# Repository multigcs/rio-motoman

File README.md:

# rio-octobot
6Axis LinuxCNC-RIO main-board - for the iceWerx iCE40-HX8K FPGA-Devboard - kicad project 
 
experimental - not tested yet

 https://youtube.com/shorts/BiJppd6_cA4

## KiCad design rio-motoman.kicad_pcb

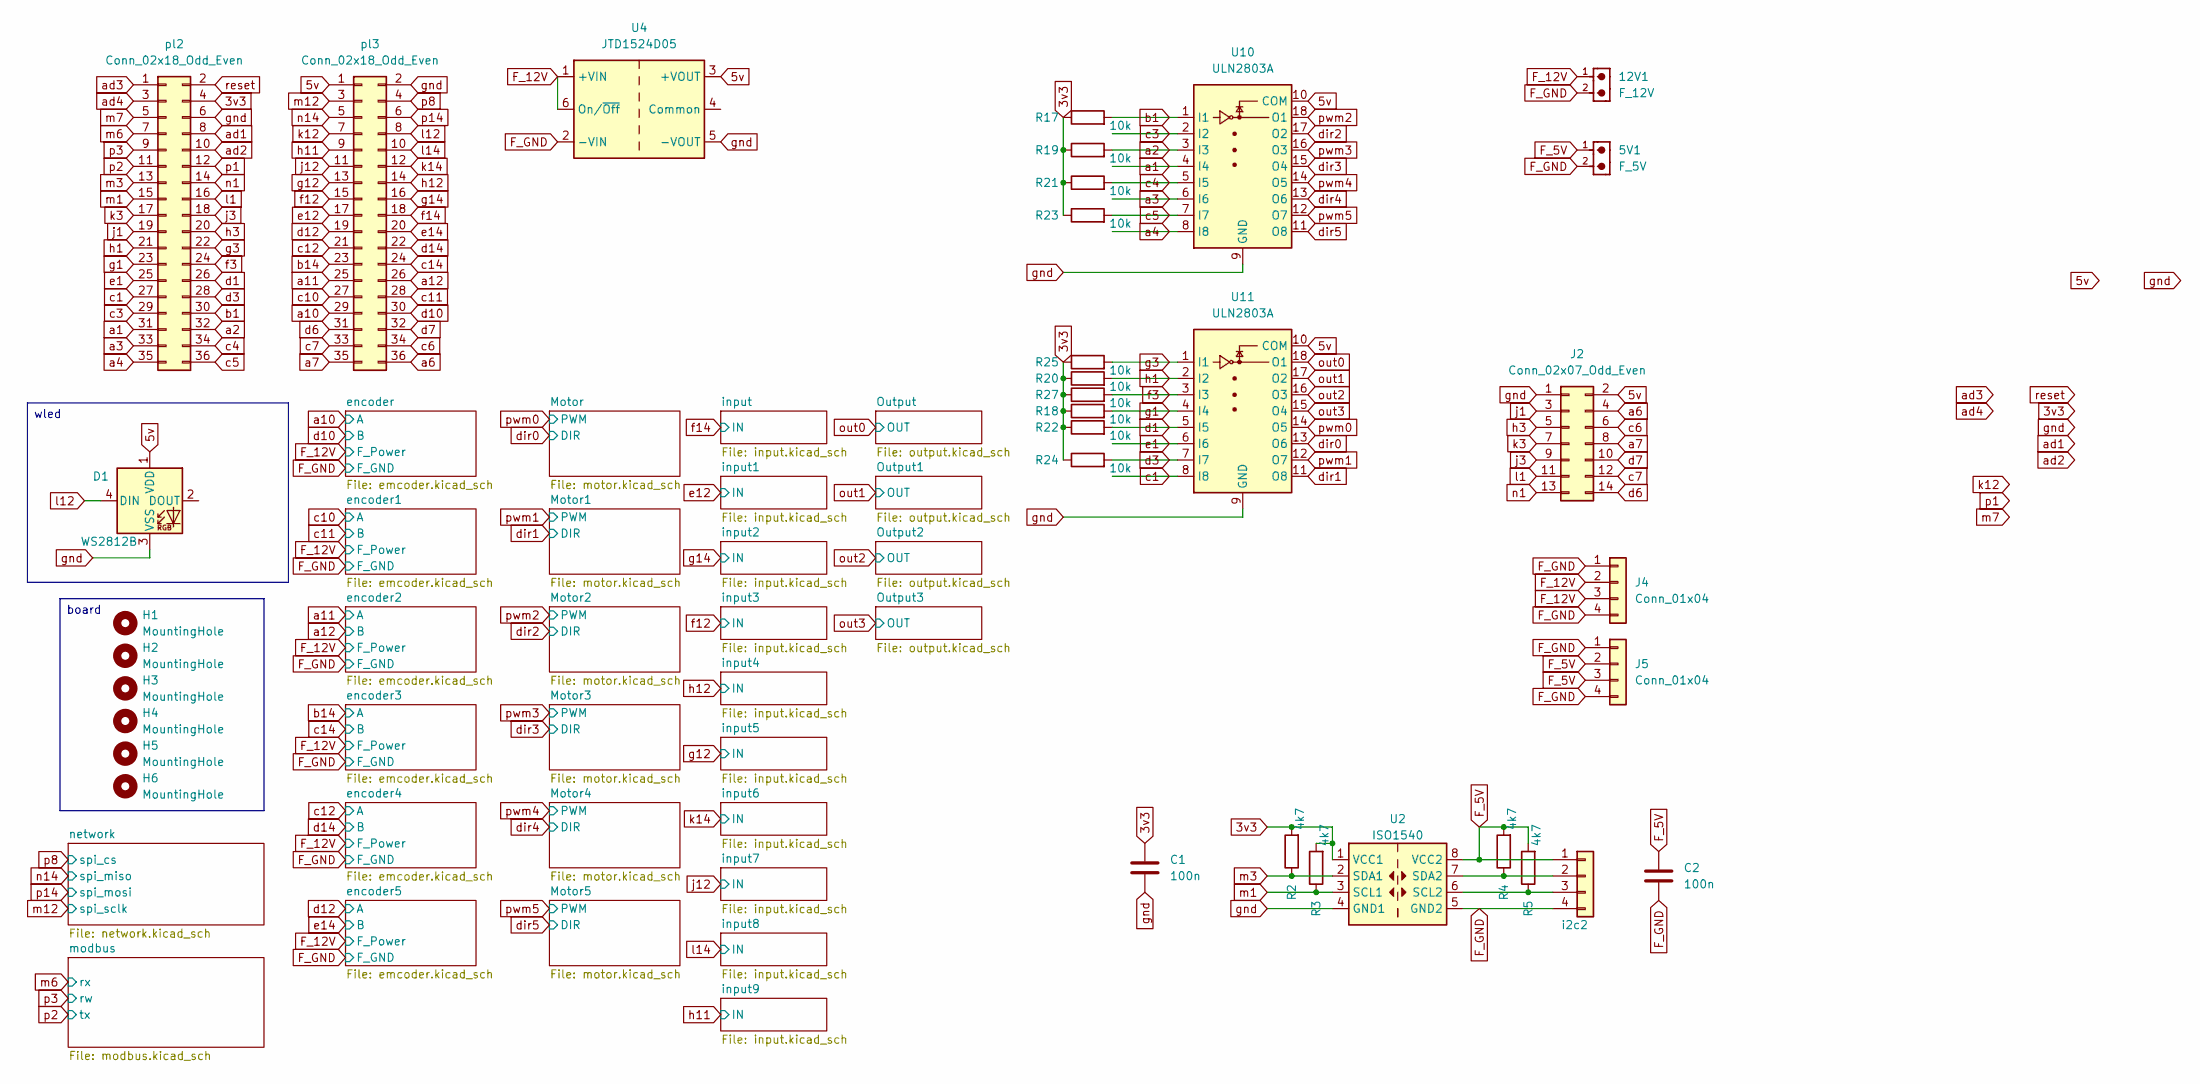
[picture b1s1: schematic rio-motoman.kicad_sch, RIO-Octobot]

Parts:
5V1: F_5V; 691322110002; PART-NUMBER 691322110002
12V1: F_12V; 691322110002; PART-NUMBER 691322110002
C1, C2: 100n; R_0805_2012Metric_Pad1.20x1.40mm_HandSolder
D1: WS2812B; LED_WS2812B_PLCC4_5.0x5.0mm_P3.2mm
H1, H2, H3, H4, H5, H6: MountingHole; MountingHole_3.2mm_M3_DIN965_Pad_TopBottom
J2: Conn_02x07_Odd_Even; PinHeader_2x07_P2.54mm_Vertical
J4, J5: Conn_01x04; PinHeader_1x04_P2.54mm_Vertical
R2, R3, R4, R5: 4k7; R_0805_2012Metric_Pad1.20x1.40mm_HandSolder
R17, R18, R19, R20, R21, R22, R23, R24, R25, R27: 10k; R_1206_3216Metric
U2: ISO1540; SOIC-8_3.9x4.9mm_P1.27mm
U4: JTD1524D05; Converter_DCDC_XP_POWER_JTDxxxxxxx_THT
U10, U11: ULN2803A; SOIC-18W_7.5x11.6mm_P1.27mm
i2c2: Conn_01x04; JST_XH_B4B-XH-A_1x04_P2.50mm_Vertical
pl2, pl3: Conn_02x18_Odd_Even; PinSocket_2x18_P2.00mm_Vertical

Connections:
3v3: C1.1, R2.2, R3.2, R17.1, R18.1, R19.1, R20.1, R21.1, R22.1, R23.1, R24.1, R25.1, R27.1, U2.1 (VCC1), pl2.4; also elsewhere on the board
5v: D1.1 (VDD), J2.2, U4.3 (+VOUT), U10.10 (COM), U11.10 (COM), pl3.1; also elsewhere on the board
F_5V: 5V1.1, C2.1, J5.2, J5.3, R4.2, R5.2, U2.8 (VCC2), i2c2.1; also elsewhere on the board
F_12V: 12V1.1, J4.2, J4.3, U4.1 (+VIN), U4.6 (On/~Off); also elsewhere on the board
F_GND: 5V1.2, 12V1.2, C2.2, J4.1, J4.4, J5.1, J5.4, U2.5 (GND2), U4.2 (-VIN), i2c2.4; also elsewhere on the board
unnamed: R5.1, U2.6 (SCL2), i2c2.3
unnamed: R4.1, U2.7 (SDA2), i2c2.2
a1: U10.4 (I4), pl2.31
a2: R19.2, U10.3 (I3), pl2.32
a3: U10.6 (I6), pl2.33
a4: U10.8 (I8), pl2.35
a6: J2.4, pl3.36
a7: J2.8, pl3.35
a10: pl3.29; also elsewhere on the board
a11: pl3.25; also elsewhere on the board
a12: pl3.26; also elsewhere on the board
ad1: pl2.8
ad2: pl2.10
ad3: pl2.1
ad4: pl2.3
b1: R17.2, U10.1 (I1), pl2.30
b14: pl3.23; also elsewhere on the board
c1: U11.8 (I8), pl2.27
c3: U10.2 (I2), pl2.29
c4: R21.2, U10.5 (I5), pl2.34
c5: R23.2, U10.7 (I7), pl2.36
c6: J2.6, pl3.34
c7: J2.12, pl3.33
c10: pl3.27; also elsewhere on the board
c11: pl3.28; also elsewhere on the board
c12: pl3.21; also elsewhere on the board
c14: pl3.24; also elsewhere on the board
d1: R22.2, U11.5 (I5), pl2.26
d3: R24.2, U11.7 (I7), pl2.28
d6: J2.14, pl3.31
d7: J2.10, pl3.32
d10: pl3.30; also elsewhere on the board
d12: pl3.19; also elsewhere on the board
d14: pl3.22; also elsewhere on the board
dir0: U11.13 (O6); also elsewhere on the board
dir1: U11.11 (O8); also elsewhere on the board
dir2: U10.17 (O2); also elsewhere on the board
dir3: U10.15 (O4); also elsewhere on the board
dir4: U10.13 (O6); also elsewhere on the board
dir5: U10.11 (O8); also elsewhere on the board
e1: U11.6 (I6), pl2.25
e12: pl3.17; also elsewhere on the board
e14: pl3.20; also elsewhere on the board
f3: R27.2, U11.3 (I3), pl2.24
f12: pl3.15; also elsewhere on the board
f14: pl3.18; also elsewhere on the board
g1: R18.2, U11.4 (I4), pl2.23
g3: R25.2, U11.1 (I1), pl2.22
g12: pl3.13; also elsewhere on the board
g14: pl3.16; also elsewhere on the board
gnd: C1.2, D1.3 (VSS), J2.1, U2.4 (GND1), U4.5 (-VOUT), U10.9 (GND), U11.9 (GND), pl2.6, pl3.2; also elsewhere on the board
h1: R20.2, U11.2 (I2), pl2.21
h3: J2.5, pl2.20
h11: pl3.9; also elsewhere on the board
h12: pl3.14; also elsewhere on the board
j1: J2.3, pl2.19
j3: J2.9, pl2.18
j12: pl3.11; also elsewhere on the board
k3: J2.7, pl2.17
k12: pl3.7
k14: pl3.12; also elsewhere on the board
l1: J2.11, pl2.16
l12: D1.4 (DIN), pl3.8
l14: pl3.10; also elsewhere on the board
m1: R3.1, U2.3 (SCL1), pl2.15
m3: R2.1, U2.2 (SDA1), pl2.13
m6: pl2.7; also elsewhere on the board
m7: pl2.5
m12: pl3.3; also elsewhere on the board
n1: J2.13, pl2.14
n14: pl3.5; also elsewhere on the board
out0: U11.18 (O1); also elsewhere on the board
out1: U11.17 (O2); also elsewhere on the board
out2: U11.16 (O3); also elsewhere on the board
out3: U11.15 (O4); also elsewhere on the board
p1: pl2.12
p2: pl2.11; also elsewhere on the board
p3: pl2.9; also elsewhere on the board
p8: pl3.4; also elsewhere on the board
p14: pl3.6; also elsewhere on the board
pwm0: U11.14 (O5); also elsewhere on the board
pwm1: U11.12 (O7); also elsewhere on the board
pwm2: U10.18 (O1); also elsewhere on the board
pwm3: U10.16 (O3); also elsewhere on the board
pwm4: U10.14 (O5); also elsewhere on the board
pwm5: U10.12 (O7); also elsewhere on the board
reset: pl2.2

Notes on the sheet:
board
wled

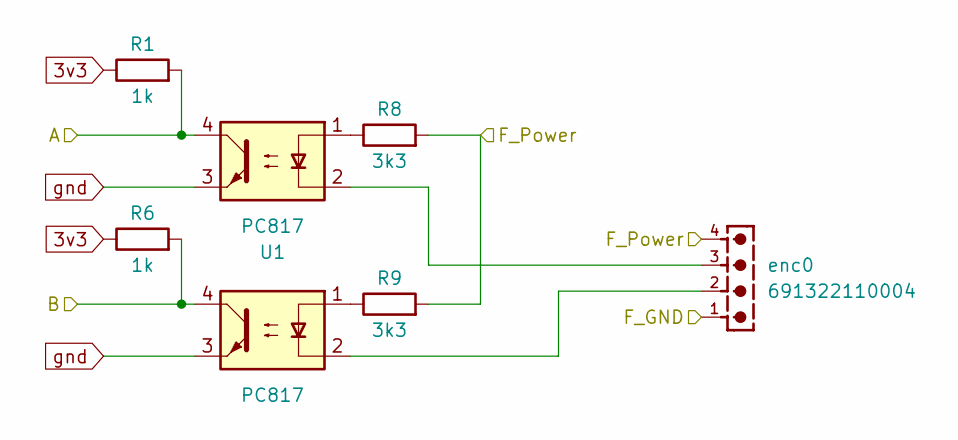
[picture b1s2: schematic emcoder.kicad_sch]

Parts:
R1, R6: 1k; R_1206_3216Metric
R8, R9: 3k3; R_1206_3216Metric
U1, U3: PC817; DIP-4_W7.62mm
enc0: 691322110004; PART-NUMBER 691322110004

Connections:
3v3: R1.1, R6.1; also elsewhere on the board
F_12V: R8.2, R9.2, enc0.4; also elsewhere on the board
F_GND: enc0.1; also elsewhere on the board
unnamed: R8.1, U1.1
unnamed: R9.1, U3.1
unnamed: U1.2, enc0.3
unnamed: U3.2, enc0.2
a10: R1.2, U1.4; also elsewhere on the board
d10: R6.2, U3.4; also elsewhere on the board
gnd: U1.3, U3.3; also elsewhere on the board

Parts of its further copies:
R11, R12, R33, R34, R39, R40, R48, R49, R54, R55: 1k; R_1206_3216Metric
R14, R15, R36, R37, R42, R43, R51, R52, R57, R58: 3k3; R_1206_3216Metric
U5, U6, U8, U9, U14, U15, U17, U18, U20, U21: PC817; DIP-4_W7.62mm
enc1, enc2, enc3, enc4, enc5: 691322110004; PART-NUMBER 691322110004

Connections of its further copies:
3v3: R11.1, R12.1, R33.1, R34.1, R39.1, R40.1, R48.1, R49.1, R54.1, R55.1; also elsewhere on the board
F_12V: R14.2, R15.2, R36.2, R37.2, R42.2, R43.2, R51.2, R52.2, R57.2, R58.2, enc1.4, enc2.4, enc3.4, enc4.4, enc5.4; also elsewhere on the board
F_GND: enc1.1, enc2.1, enc3.1, enc4.1, enc5.1; also elsewhere on the board
unnamed: R14.1, U5.1
unnamed: R15.1, U6.1
unnamed: R36.1, U8.1
unnamed: R37.1, U9.1
unnamed: R42.1, U14.1
unnamed: R43.1, U15.1
unnamed: R51.1, U17.1
unnamed: R52.1, U18.1
unnamed: R57.1, U20.1
unnamed: R58.1, U21.1
unnamed: U5.2, enc1.3
unnamed: U6.2, enc1.2
unnamed: U8.2, enc2.3
unnamed: U9.2, enc2.2
unnamed: U14.2, enc3.3
unnamed: U15.2, enc3.2
unnamed: U17.2, enc4.3
unnamed: U18.2, enc4.2
unnamed: U20.2, enc5.3
unnamed: U21.2, enc5.2
a11: R33.2, U8.4; also elsewhere on the board
a12: R34.2, U9.4; also elsewhere on the board
b14: R39.2, U14.4; also elsewhere on the board
c10: R11.2, U5.4; also elsewhere on the board
c11: R12.2, U6.4; also elsewhere on the board
c12: R48.2, U17.4; also elsewhere on the board
c14: R40.2, U15.4; also elsewhere on the board
d12: R54.2, U20.4; also elsewhere on the board
d14: R49.2, U18.4; also elsewhere on the board
e14: R55.2, U21.4; also elsewhere on the board
gnd: U5.3, U6.3, U8.3, U9.3, U14.3, U15.3, U17.3, U18.3, U20.3, U21.3; also elsewhere on the board

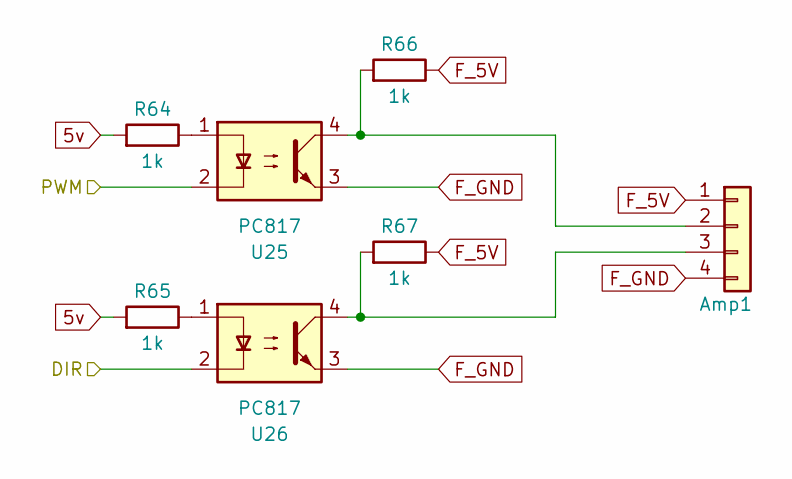
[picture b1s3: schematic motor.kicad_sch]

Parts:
Amp1: Conn_01x04; JST_XH_B4B-XH-A_1x04_P2.50mm_Vertical
R64, R65, R66, R67: 1k; R_1206_3216Metric
U25, U26: PC817; DIP-4_W7.62mm

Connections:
5v: R64.2, R65.2; also elsewhere on the board
F_5V: Amp1.1, R66.1, R67.1; also elsewhere on the board
F_GND: Amp1.4, U25.3, U26.3; also elsewhere on the board
unnamed: Amp1.2, R66.2, U25.4
unnamed: Amp1.3, R67.2, U26.4
unnamed: R64.1, U25.1
unnamed: R65.1, U26.1
dir1: U26.2; also elsewhere on the board
pwm1: U25.2; also elsewhere on the board

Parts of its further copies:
Amp0, Amp2, Amp3, Amp4, Amp5: Conn_01x04; JST_XH_B4B-XH-A_1x04_P2.50mm_Vertical
R60, R61, R62, R63, R68, R69, R70, R71, R72, R73, R74, R75, R76, R77, R78, R79, R80, R81, R82, R83: 1k; R_1206_3216Metric
U23, U24, U27, U28, U29, U30, U31, U32, U33, U34: PC817; DIP-4_W7.62mm

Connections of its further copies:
5v: R61.2, R62.2, R68.2, R69.2, R72.2, R73.2, R76.2, R77.2, R80.2, R81.2; also elsewhere on the board
F_5V: Amp0.1, Amp2.1, Amp3.1, Amp4.1, Amp5.1, R60.1, R63.1, R70.1, R71.1, R74.1, R75.1, R78.1, R79.1, R82.1, R83.1; also elsewhere on the board
F_GND: Amp0.4, Amp2.4, Amp3.4, Amp4.4, Amp5.4, U23.3, U24.3, U27.3, U28.3, U29.3, U30.3, U31.3, U32.3, U33.3, U34.3; also elsewhere on the board
unnamed: Amp0.2, R60.2, U23.4
unnamed: Amp0.3, R63.2, U24.4
unnamed: Amp2.2, R70.2, U27.4
unnamed: Amp2.3, R71.2, U28.4
unnamed: Amp3.2, R74.2, U29.4
unnamed: Amp3.3, R75.2, U30.4
unnamed: Amp4.2, R78.2, U31.4
unnamed: Amp4.3, R79.2, U32.4
unnamed: Amp5.2, R82.2, U33.4
unnamed: Amp5.3, R83.2, U34.4
unnamed: R61.1, U23.1
unnamed: R62.1, U24.1
unnamed: R68.1, U27.1
unnamed: R69.1, U28.1
unnamed: R72.1, U29.1
unnamed: R73.1, U30.1
unnamed: R76.1, U31.1
unnamed: R77.1, U32.1
unnamed: R80.1, U33.1
unnamed: R81.1, U34.1
dir0: U24.2; also elsewhere on the board
dir2: U28.2; also elsewhere on the board
dir3: U30.2; also elsewhere on the board
dir4: U32.2; also elsewhere on the board
dir5: U34.2; also elsewhere on the board
pwm0: U23.2; also elsewhere on the board
pwm2: U27.2; also elsewhere on the board
pwm3: U29.2; also elsewhere on the board
pwm4: U31.2; also elsewhere on the board
pwm5: U33.2; also elsewhere on the board

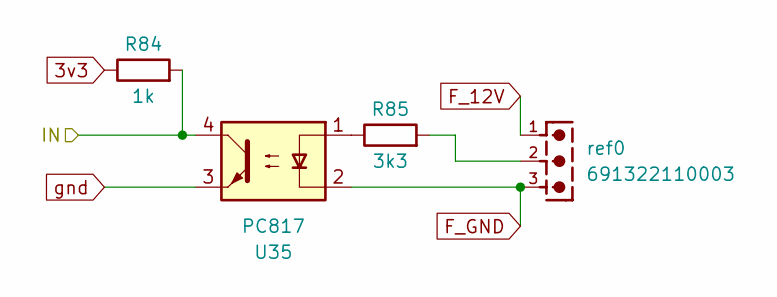
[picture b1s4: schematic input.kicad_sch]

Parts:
R84: 1k; R_1206_3216Metric
R85: 3k3; R_1206_3216Metric
U35: PC817; DIP-4_W7.62mm
ref0: 691322110003; PART-NUMBER 691322110003

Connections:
3v3: R84.1; also elsewhere on the board
F_12V: ref0.1; also elsewhere on the board
F_GND: U35.2, ref0.3; also elsewhere on the board
unnamed: R85.1, U35.1
unnamed: R85.2, ref0.2
f14: R84.2, U35.4; also elsewhere on the board
gnd: U35.3; also elsewhere on the board

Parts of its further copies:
R86, R88, R90, R92, R94, R96, R98, R100, R110: 1k; R_1206_3216Metric
R87, R89, R91, R93, R95, R97, R99, R101, R111: 3k3; R_1206_3216Metric
U36, U37, U38, U39, U40, U41, U42, U43, U48: PC817; DIP-4_W7.62mm
in0, in1, in2, in3: 691322110003; PART-NUMBER 691322110003
ref1, ref2, ref3, ref4, ref5: 691322110003; PART-NUMBER 691322110003

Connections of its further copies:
3v3: R86.1, R88.1, R90.1, R92.1, R94.1, R96.1, R98.1, R100.1, R110.1; also elsewhere on the board
F_12V: in0.1, in1.1, in2.1, in3.1, ref1.1, ref2.1, ref3.1, ref4.1, ref5.1; also elsewhere on the board
F_GND: U36.2, U37.2, U38.2, U39.2, U40.2, U41.2, U42.2, U43.2, U48.2, in0.3, in1.3, in2.3, in3.3, ref1.3, ref2.3, ref3.3, ref4.3, ref5.3; also elsewhere on the board
unnamed: R87.1, U36.1
unnamed: R87.2, ref1.2
unnamed: R89.1, U37.1
unnamed: R89.2, ref2.2
unnamed: R91.1, U38.1
unnamed: R91.2, ref3.2
unnamed: R93.1, U39.1
unnamed: R93.2, ref4.2
unnamed: R95.1, U40.1
unnamed: R95.2, ref5.2
unnamed: R97.1, U41.1
unnamed: R97.2, in0.2
unnamed: R99.1, U42.1
unnamed: R99.2, in1.2
unnamed: R101.1, U43.1
unnamed: R101.2, in2.2
unnamed: R111.1, U48.1
unnamed: R111.2, in3.2
e12: R86.2, U36.4; also elsewhere on the board
f12: R90.2, U38.4; also elsewhere on the board
g12: R94.2, U40.4; also elsewhere on the board
g14: R88.2, U37.4; also elsewhere on the board
gnd: U36.3, U37.3, U38.3, U39.3, U40.3, U41.3, U42.3, U43.3, U48.3; also elsewhere on the board
h11: R110.2, U48.4; also elsewhere on the board
h12: R92.2, U39.4; also elsewhere on the board
j12: R98.2, U42.4; also elsewhere on the board
k14: R96.2, U41.4; also elsewhere on the board
l14: R100.2, U43.4; also elsewhere on the board

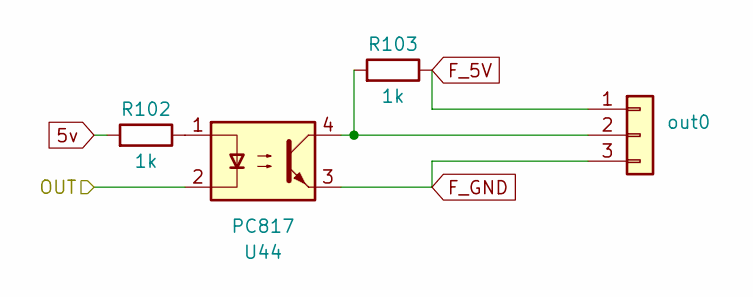
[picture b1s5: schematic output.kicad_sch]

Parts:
R102, R103: 1k; R_1206_3216Metric
U44: PC817; DIP-4_W7.62mm
out0: Conn_01x03; JST_XH_B3B-XH-A_1x03_P2.50mm_Vertical

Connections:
5v: R102.2; also elsewhere on the board
F_5V: R103.1, out0.1; also elsewhere on the board
F_GND: U44.3, out0.3; also elsewhere on the board
unnamed: R102.1, U44.1
unnamed: R103.2, U44.4, out0.2
out0: U44.2; also elsewhere on the board

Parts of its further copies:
R104, R105, R106, R107, R108, R109: 1k; R_1206_3216Metric
U45, U46, U47: PC817; DIP-4_W7.62mm
out1, out2, out3: Conn_01x03; JST_XH_B3B-XH-A_1x03_P2.50mm_Vertical

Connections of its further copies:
5v: R104.2, R106.2, R108.2; also elsewhere on the board
F_5V: R105.1, R107.1, R109.1, out1.1, out2.1, out3.1; also elsewhere on the board
F_GND: U45.3, U46.3, U47.3, out1.3, out2.3, out3.3; also elsewhere on the board
unnamed: R104.1, U45.1
unnamed: R106.1, U46.1
unnamed: R108.1, U47.1
unnamed: R105.2, U45.4, out1.2
unnamed: R107.2, U46.4, out2.2
unnamed: R109.2, U47.4, out3.2
out1: U45.2; also elsewhere on the board
out2: U46.2; also elsewhere on the board
out3: U47.2; also elsewhere on the board

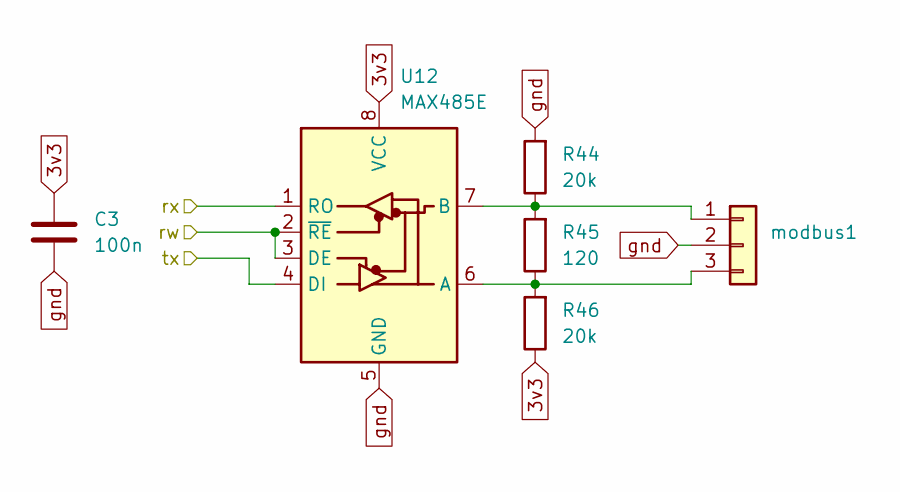
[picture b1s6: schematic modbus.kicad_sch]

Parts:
C3: 100n; C_1206_3216Metric
R44, R46: 20k; R_1206_3216Metric
R45: 120; R_1206_3216Metric
U12: MAX485E; Diodes_SO-8EP
modbus1: Conn_01x03; JST_XH_B3B-XH-A_1x03_P2.50mm_Vertical

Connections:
3v3: C3.1, R46.1, U12.8 (VCC); also elsewhere on the board
unnamed: R45.1, R46.2, U12.6 (A), modbus1.3
unnamed: R44.1, R45.2, U12.7 (B), modbus1.1
gnd: C3.2, R44.2, U12.5 (GND), modbus1.2; also elsewhere on the board
m6: U12.1 (RO); also elsewhere on the board
p2: U12.4 (DI); also elsewhere on the board
p3: U12.2 (~RE), U12.3 (DE); also elsewhere on the board

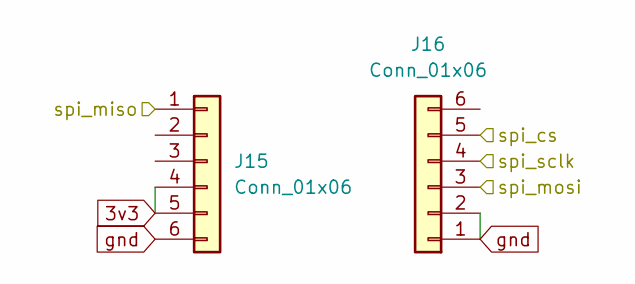
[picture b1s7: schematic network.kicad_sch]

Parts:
J15, J16: Conn_01x06; PinSocket_1x06_P2.54mm_Vertical

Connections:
3v3: J15.4, J15.5; also elsewhere on the board
gnd: J15.6, J16.1, J16.2; also elsewhere on the board
m12: J16.4; also elsewhere on the board
n14: J15.1; also elsewhere on the board
p8: J16.5; also elsewhere on the board
p14: J16.3; also elsewhere on the board

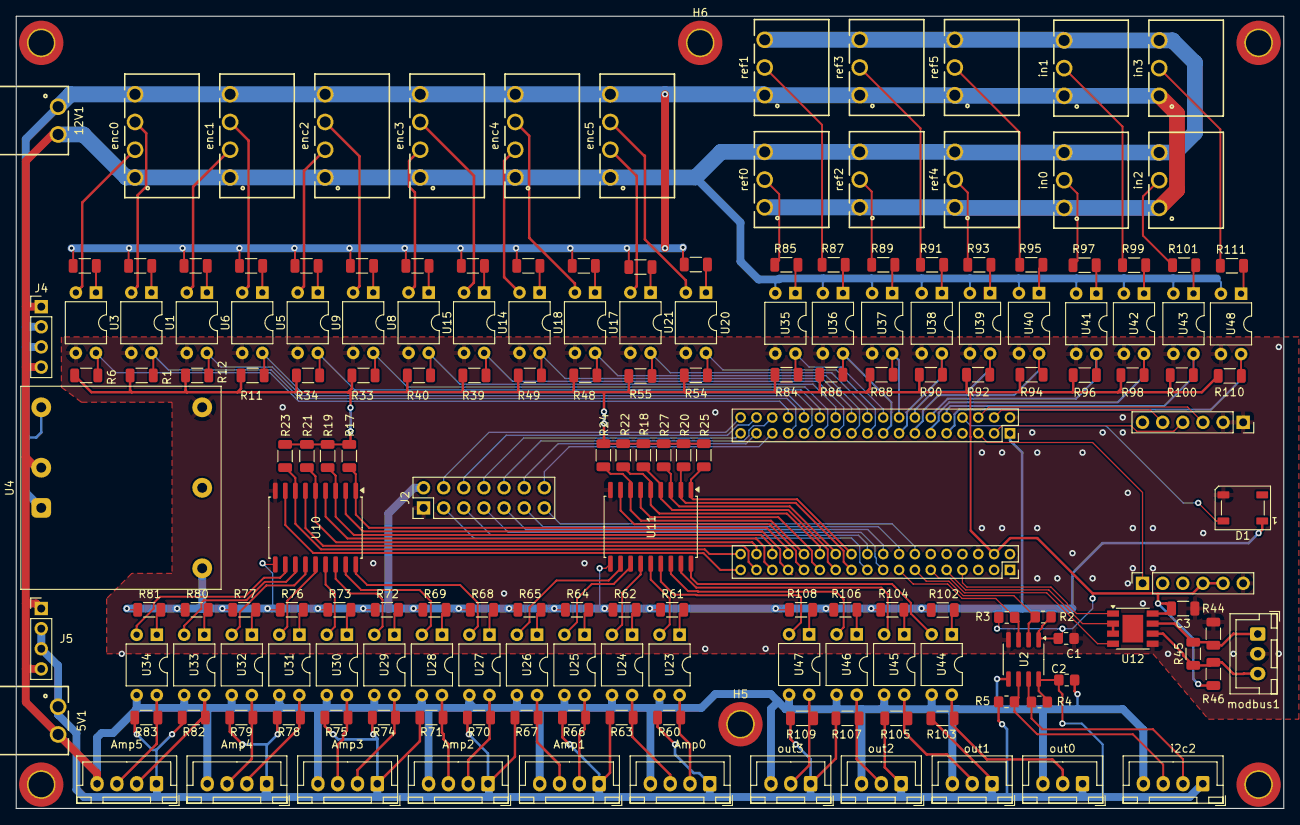
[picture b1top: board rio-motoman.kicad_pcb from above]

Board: 2 copper layers, 160.0 x 100.0 mm, 183 parts (0 on the bottom side), 162 nets.

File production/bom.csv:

Designator,Footprint,Quantity,Value,LCSC Part #
12V1,691322110002,1,F_12V,
5V1,691322110002,1,F_5V,
"AMP0, AMP1, AMP2, AMP3, AMP4, AMP5, I2C2",JST_XH_B4B-XH-A_1x04_P2.50mm_Vertical,7,Conn_01x04,
"C1, C2",0805,2,100n,
C3,1206,1,100n,
D1,LED_WS2812B_PLCC4_5.0x5.0mm_P3.2mm,1,WS2812B,
"ENC0, ENC1, ENC2, ENC3, ENC4, ENC5",691322110004,6,691322110004,
"H1, H2, H3, H4, H5, H6",MountingHole_3.2mm_M3_DIN965_Pad_TopBottom,6,MountingHole,
"IN0, IN1, IN2, IN3, REF0, REF1, REF2, REF3, REF4, REF5",691322110003,10,691322110003,
"J15, J16",PinSocket_1x06_P2.54mm_Vertical,2,Conn_01x06,
J2,PinHeader_2x07_P2.54mm_Vertical,1,Conn_02x07_Odd_Even,
"J4, J5",PinHeader_1x04_P2.54mm_Vertical,2,Conn_01x04,
"MODBUS1, OUT0, OUT1, OUT2, OUT3",JST_XH_B3B-XH-A_1x03_P2.50mm_Vertical,5,Conn_01x03,
"PL2, PL3",PinSocket_2x18_P2.00mm_Vertical,2,Conn_02x18_Odd_Even,
"R1, R100, R102, R103, R104, R105, R106, R107, R108, R109, R11, R110, R12, R33, R34, R39, R40, R48, R49, R54, R55, R6, R60, R61, R62, R63, R64, R65, R66, R67, R68, R69, R70, R71, R72, R73, R74, R75, R76, R77, R78, R79, R80, R81, R82, R83, R84, R86, R88, R90, R92, R94, R96, R98",1206,54,1k,
"R101, R111, R14, R15, R36, R37, R42, R43, R51, R52, R57, R58, R8, R85, R87, R89, R9, R91, R93, R95, R97, R99",1206,22,3k3,
"R17, R18, R19, R20, R21, R22, R23, R24, R25, R27",1206,10,10k,
"R2, R3, R4, R5",0805,4,4k7,
"R44, R46",1206,2,20k,
R45,1206,1,120,
"U1, U14, U15, U17, U18, U20, U21, U23, U24, U25, U26, U27, U28, U29, U3, U30, U31, U32, U33, U34, U35, U36, U37, U38, U39, U40, U41, U42, U43, U44, U45, U46, U47, U48, U5, U6, U8, U9",DIP-4_W7.62mm,38,PC817,
"U10, U11",SOIC-18W_7.5x11.6mm_P1.27mm,2,ULN2803A,
U12,Diodes_SO-8EP,1,MAX485E,
U2,SOIC-8_3.9x4.9mm_P1.27mm,1,ISO1540,
U4,Converter_DCDC_XP_POWER_JTDxxxxxxx_THT,1,JTD1524D05,

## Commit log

2025-04-25 initial release
2025-05-07 little fix / adding images
